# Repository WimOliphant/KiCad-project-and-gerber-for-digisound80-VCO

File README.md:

# KiCad-project-and-gerber-for-digisound80-VCO

Untested PCB gerbers. There could be errors. 

Via https://www.eddybergman.com/2020/01/synthesizer-build-part-18-really-good.html

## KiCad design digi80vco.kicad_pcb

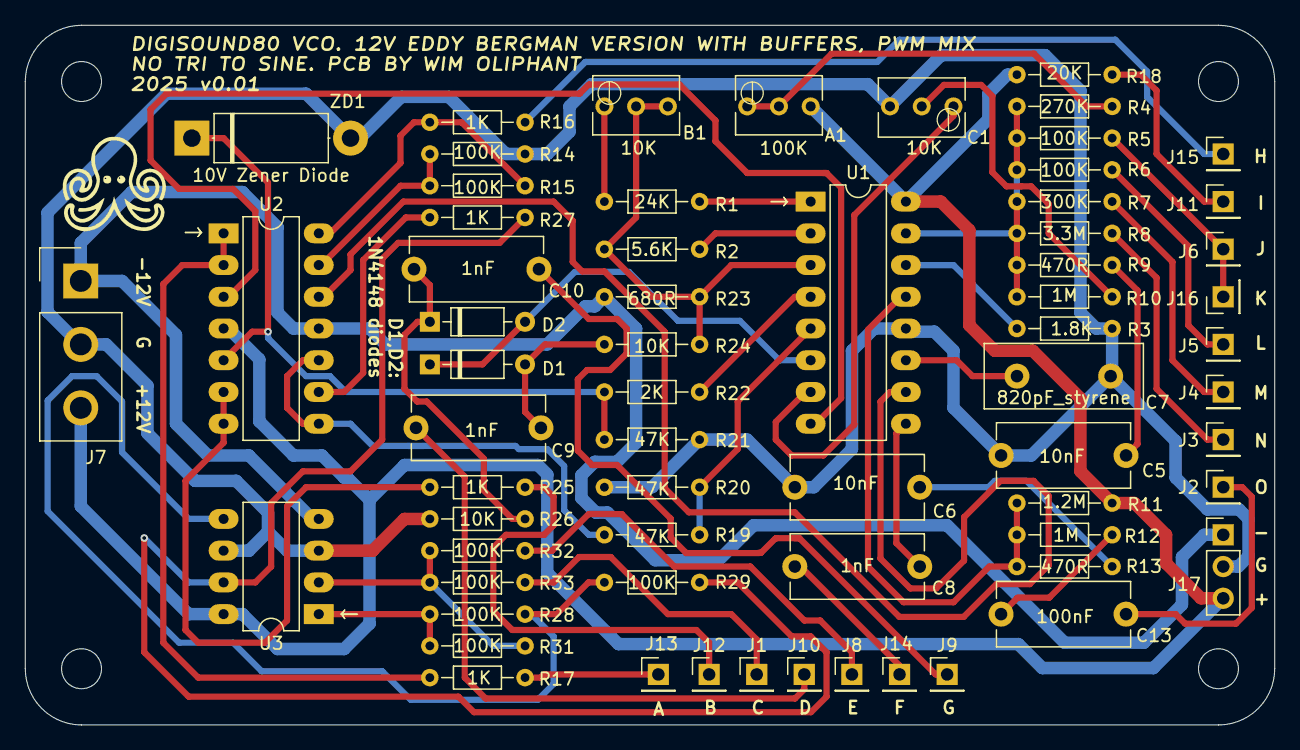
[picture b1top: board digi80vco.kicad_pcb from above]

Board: 2 copper layers, 100.0 x 56.0 mm, 65 parts (0 on the bottom side), 50 nets.

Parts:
A1: 100K; Potentiometer_Bourns_3266Y_Vertical
B1: 10K; Potentiometer_Bourns_3266Y_Vertical
C1: 10K; Potentiometer_Bourns_3266Y_Vertical
C5, C6: 10nF; C_Disc_D10.5mm_W5.0mm_P10.00mm
C7: 820pF_styrene; C_Disc_D12.5mm_W5.0mm_P7.50mm
C8, C9, C10: 1nF; C_Disc_D10.5mm_W5.0mm_P10.00mm
C13: 100nF; C_Disc_D10.5mm_W5.0mm_P10.00mm
D1, D2: 1N4148; D_DO-35_SOD27_P7.62mm_Horizontal
J1: rv4_pin2; PinHeader_1x01_P2.54mm_Vertical
J2: to_rv3_pot; PinHeader_1x01_P2.54mm_Vertical
J3: to_rv2; PinHeader_1x01_P2.54mm_Vertical
J4: to_s1_switch; PinHeader_1x01_P2.54mm_Vertical
J5: to_rv5_pot; PinHeader_1x01_P2.54mm_Vertical
J6: 1v_oct_in_1_jack; PinHeader_1x01_P2.54mm_Vertical
J7: power input; Samtec_HPM-03-01-x-S_Straight_1x03_Pitch5.08mm
J8: external_pulse_width_mod_cv_in_jack; PinHeader_1x01_P2.54mm_Vertical
J9: neg_hard_sync_in_jack; PinHeader_1x01_P2.54mm_Vertical
J10: pos_hard_sync_in; PinHeader_1x01_P2.54mm_Vertical
J11: rv4_pin3; PinHeader_1x01_P2.54mm_Vertical
J12: square_out_jack; PinHeader_1x01_P2.54mm_Vertical
J13: saw_out_jack; PinHeader_1x01_P2.54mm_Vertical
J14: soft_sync_in_jack; PinHeader_1x01_P2.54mm_Vertical
J15: triangle_ouput_jack; PinHeader_1x01_P2.54mm_Vertical
J16: 1v_oct_in_2_jack; PinHeader_1x01_P2.54mm_Vertical
J17: power output; PinHeader_1x03_P2.54mm_Vertical
R1: 24K; R_Axial_DIN0204_L3.6mm_D1.6mm_P7.62mm_Horizontal
R2: 5.6K; R_Axial_DIN0204_L3.6mm_D1.6mm_P7.62mm_Horizontal
R3: 1.8K; R_Axial_DIN0204_L3.6mm_D1.6mm_P7.62mm_Horizontal
R4: 270K; R_Axial_DIN0204_L3.6mm_D1.6mm_P7.62mm_Horizontal
R5, R6, R14, R15, R28, R29, R31, R32, R33: 100K; R_Axial_DIN0204_L3.6mm_D1.6mm_P7.62mm_Horizontal
R7: 300K; R_Axial_DIN0204_L3.6mm_D1.6mm_P7.62mm_Horizontal
R8: 3.3M; R_Axial_DIN0204_L3.6mm_D1.6mm_P7.62mm_Horizontal
R9, R13: 470R; R_Axial_DIN0204_L3.6mm_D1.6mm_P7.62mm_Horizontal
R10, R12: 1M; R_Axial_DIN0204_L3.6mm_D1.6mm_P7.62mm_Horizontal
R11: 1.2M; R_Axial_DIN0204_L3.6mm_D1.6mm_P7.62mm_Horizontal
R16, R17, R25, R27: 1K; R_Axial_DIN0204_L3.6mm_D1.6mm_P7.62mm_Horizontal
R18: 20K; R_Axial_DIN0204_L3.6mm_D1.6mm_P7.62mm_Horizontal
R19, R20, R21: 47K; R_Axial_DIN0204_L3.6mm_D1.6mm_P7.62mm_Horizontal
R22: 2K; R_Axial_DIN0204_L3.6mm_D1.6mm_P7.62mm_Horizontal
R23: 680R; R_Axial_DIN0204_L3.6mm_D1.6mm_P7.62mm_Horizontal
R24, R26: 10K; R_Axial_DIN0204_L3.6mm_D1.6mm_P7.62mm_Horizontal
U1: AS3340; DIP-16_W7.62mm_LongPads
U2: TL074; DIP-14_W7.62mm_LongPads
U3: TL072; DIP-8_W7.62mm_LongPads
ZD1: 10V Zener Diode; D_5W_P12.70mm_Horizontal

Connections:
+12V: A1.3, J7.3, J17.3, R11.2, R18.2, U1.16 (VCC), U2.4 (V+), U3.8 (V+)
-12V: J7.1, J17.1, R23.1, U2.11 (V-), U3.4 (V-)
/3340_1: R1.2, U1.1 (SCALE1)
/3340_2: R2.2, U1.2 (SCALE2)
/3340_3: B1.2, B1.3, R2.1, R23.2, R24.2, U1.3 (VEE)
/3340_4: R22.2, U1.4 (VP)
/3340_5: R19.2, R20.2, U1.5 (VPWM)
/3340_6: D1.1 (K), D2.2 (A), U1.6 (VHSI)
/3340_7: C1.1, U1.7 (VHFT)
/3340_8: U1.8 (VSO), U2.3 (+)
/3340_9: C8.1, U1.9 (VSSI)
/3340_10: U1.10 (VTO), U2.12 (+)
/3340_11: C7.1, U1.11 (CAP)
/3340_13: R11.1, R12.1, R13.1, U1.13 (VLFI)
/3340_14: R3.1, U1.14 (VS)
/3340_15: R4.1, R5.1, R6.1, R7.1, R8.1, R9.1, R10.2, U1.15 (VFCI)
GND: C1.3, C5.2, C6.2, C7.2, J7.2, J17.2, R3.2, R14.1, R20.1, R21.1, R26.1, U1.12 (GND), U3.3 (+), U3.6 (-), ZD1.2 (A)
unnamed: C5.1, R9.2
unnamed: C6.1, R13.2
unnamed: C13.1, R12.2
unnamed: C9.2, D1.2 (A), R24.1
unnamed: C10.2, D2.1 (K), R26.2
unnamed: J1.1, R33.1
unnamed: C13.2, J2.1
unnamed: J3.1, R8.2
unnamed: J4.1, R7.2
unnamed: J5.1, R6.2
unnamed: J8.1, R32.1
unnamed: C10.1, J9.1
unnamed: C9.1, J10.1
unnamed: J11.1, R18.1
unnamed: J12.1, R25.1
unnamed: J13.1, R17.2
unnamed: C8.2, J14.1
unnamed: J15.1, R16.2
unnamed: J6.1, J16.1, R5.2
unnamed: B1.1, R1.1
unnamed: A1.1, A1.2, R4.2
unnamed: C1.2, R10.1
unnamed: R15.2, R16.1, U2.14
unnamed: R27.2, R29.2, U3.7
unnamed: R28.1, R31.2, U3.1
unnamed: R17.1, U2.1, U2.2 (-)
unnamed: R21.2, R22.1, U2.5 (+), ZD1.1 (K)
unnamed: R25.2, U2.6 (-), U2.7
unnamed: R19.1, U2.8, U2.10 (+)
unnamed: R27.1, U2.9 (-)
unnamed: R14.2, R15.1, U2.13 (-)
unnamed: R31.1, R32.2, R33.2, U3.2 (-)
unnamed: R28.2, R29.1, U3.5 (+)

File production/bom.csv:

Designator,Footprint,Quantity,Value,LCSC Part #
A1,Potentiometer_Bourns_3266Y_Vertical,1,100K,
"B1, C1",Potentiometer_Bourns_3266Y_Vertical,2,10K,
"C10, C8, C9",C_Disc_D10.5mm_W5.0mm_P10.00mm,3,1nF,
C13,C_Disc_D10.5mm_W5.0mm_P10.00mm,1,100nF,
"C5, C6",C_Disc_D10.5mm_W5.0mm_P10.00mm,2,10nF,
C7,C_Disc_D12.5mm_W5.0mm_P7.50mm,1,820pF_styrene,
"D1, D2",D_DO-35_SOD27_P7.62mm_Horizontal,2,1N4148,
J1,PinHeader_1x01_P2.54mm_Vertical,1,rv4_pin2,
J10,PinHeader_1x01_P2.54mm_Vertical,1,pos_hard_sync_in,
J11,PinHeader_1x01_P2.54mm_Vertical,1,rv4_pin3,
J12,PinHeader_1x01_P2.54mm_Vertical,1,square_out_jack,
J13,PinHeader_1x01_P2.54mm_Vertical,1,saw_out_jack,
J14,PinHeader_1x01_P2.54mm_Vertical,1,soft_sync_in_jack,
J15,PinHeader_1x01_P2.54mm_Vertical,1,triangle_ouput_jack,
J16,PinHeader_1x01_P2.54mm_Vertical,1,1v_oct_in_2_jack,
J17,PinHeader_1x03_P2.54mm_Vertical,1,power output,
J2,PinHeader_1x01_P2.54mm_Vertical,1,to_rv3_pot,
J3,PinHeader_1x01_P2.54mm_Vertical,1,to_rv2,
J4,PinHeader_1x01_P2.54mm_Vertical,1,to_s1_switch,
J5,PinHeader_1x01_P2.54mm_Vertical,1,to_rv5_pot,
J6,PinHeader_1x01_P2.54mm_Vertical,1,1v_oct_in_1_jack,
J7,Samtec_HPM-03-01-x-S_Straight_1x03_Pitch5.08mm,1,power input,
J8,PinHeader_1x01_P2.54mm_Vertical,1,external_pulse_width_mod_cv_in_jack,
J9,PinHeader_1x01_P2.54mm_Vertical,1,neg_hard_sync_in_jack,
R1,R_Axial_DIN0204_L3.6mm_D1.6mm_P7.62mm_Horizontal,1,24K,
"R10, R12",R_Axial_DIN0204_L3.6mm_D1.6mm_P7.62mm_Horizontal,2,1M,
R11,R_Axial_DIN0204_L3.6mm_D1.6mm_P7.62mm_Horizontal,1,1.2M,
"R13, R9",R_Axial_DIN0204_L3.6mm_D1.6mm_P7.62mm_Horizontal,2,470R,
"R14, R15, R28, R29, R31, R32, R33, R5, R6",R_Axial_DIN0204_L3.6mm_D1.6mm_P7.62mm_Horizontal,9,100K,
"R16, R17, R25, R27",R_Axial_DIN0204_L3.6mm_D1.6mm_P7.62mm_Horizontal,4,1K,
R18,R_Axial_DIN0204_L3.6mm_D1.6mm_P7.62mm_Horizontal,1,20K,
"R19, R20, R21",R_Axial_DIN0204_L3.6mm_D1.6mm_P7.62mm_Horizontal,3,47K,
R2,R_Axial_DIN0204_L3.6mm_D1.6mm_P7.62mm_Horizontal,1,5.6K,
R22,R_Axial_DIN0204_L3.6mm_D1.6mm_P7.62mm_Horizontal,1,2K,
R23,R_Axial_DIN0204_L3.6mm_D1.6mm_P7.62mm_Horizontal,1,680R,
"R24, R26",R_Axial_DIN0204_L3.6mm_D1.6mm_P7.62mm_Horizontal,2,10K,
R3,R_Axial_DIN0204_L3.6mm_D1.6mm_P7.62mm_Horizontal,1,1.8K,
R4,R_Axial_DIN0204_L3.6mm_D1.6mm_P7.62mm_Horizontal,1,270K,
R7,R_Axial_DIN0204_L3.6mm_D1.6mm_P7.62mm_Horizontal,1,300K,
R8,R_Axial_DIN0204_L3.6mm_D1.6mm_P7.62mm_Horizontal,1,3.3M,
U1,DIP-16_W7.62mm_LongPads,1,AS3340,
U2,DIP-14_W7.62mm_LongPads,1,TL074,
U3,DIP-8_W7.62mm_LongPads,1,TL072,
ZD1,D_5W_P12.70mm_Horizontal,1,10V Zener Diode,
